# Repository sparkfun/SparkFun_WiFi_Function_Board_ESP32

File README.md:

SparkFun WiFi Function Board - ESP32
========================================

[*SparkFun WiFi Function Board - ESP32 (WRL-18430)*](https://www.sparkfun.com/products/18430)

The SparkFun MicroMod ESP32 Function Board adds additional wireless options to MicroMod Processor Boards that do not have that capability. This special function board acts as a coprocessor that takes advantage of Espressif's ESP32 WROOM to add WiFi and Bluetooth&reg; to your applications. 

At the core of the ESP32 WROOM module is the ESP32-D0WD-V3 chip which is designed to be both scalable and adaptive. ESP32 WROOM module on this board  features 16MB of flash memory, 520kB of internal SRAM, an integrated 802.11 b/g/n WiFi transceiver, and dual-mode Bluetooth capabilities. Utilizing our handy M.2 MicroMod connector, no soldering is required to connect it to your system. Simply match up the key on your processor and function board's beveled edge connector to their respective key on the M.2 connector, then secure them to the main board with screws. The ESP32 WROOM module can then be controlled using AT commands via the serial UART port.

The ESP32 Function Board comes pre-flashed with AT-command firmware and acts as a serial-to-WiFi gateway. Next to the module is a USB-C connector and CP2102 USB-to-serial converter. Whether you want to add AT commands of your own, or flash custom firmware on the ESP32, you can use this port to reprogram the ESP32.

Repository Contents
-------------------

* **/Hardware** - Eagle design files (.brd, .sch)
* **/Production** - Production panel files (.brd)

Documentation
--------------

* **[Hookup Guide](https://learn.sparkfun.com/tutorials/1998)** - Basic hookup guide

Product Versions
----------------

* [WRL-18430](https://www.sparkfun.com/products/18430) - Initial release

Version History
---------------

* v1.0 - Initial Release

License Information
-------------------

This product is _**open source**_! 

Please review the LICENSE.md file for license information. 

If you have any questions or concerns on licensing, please contact technical support on our [SparkFun forums](https://forum.sparkfun.com/viewforum.php?f=152).

Distributed as-is; no warranty is given.

- Your friends at SparkFun.

_<COLLABORATION CREDIT>_

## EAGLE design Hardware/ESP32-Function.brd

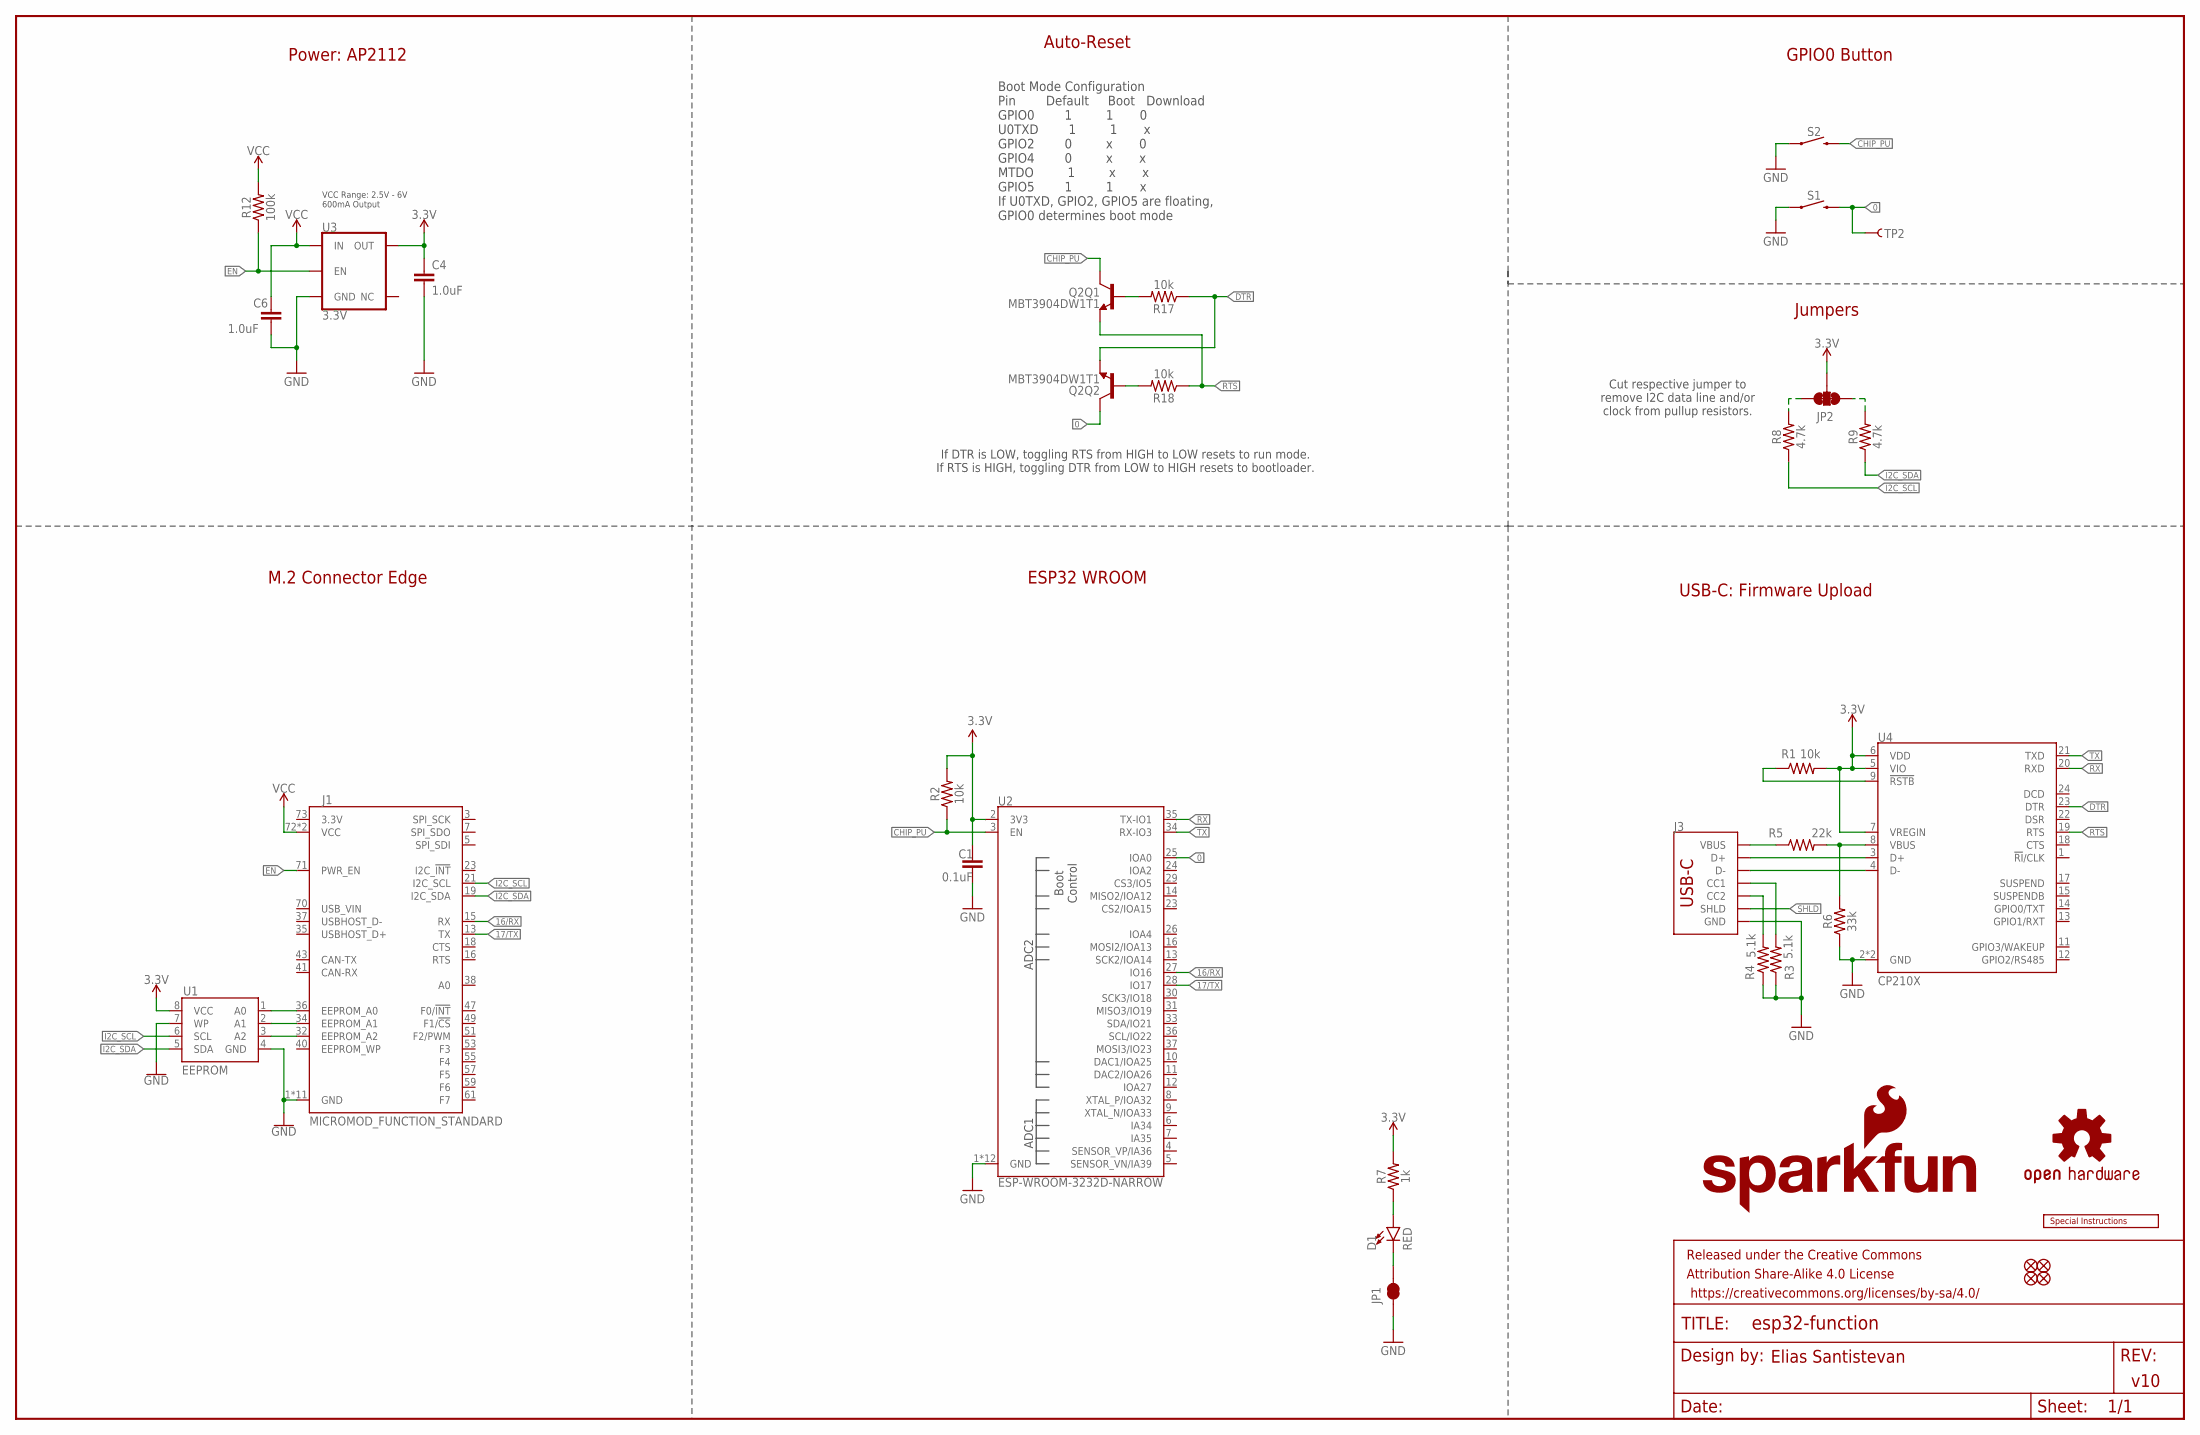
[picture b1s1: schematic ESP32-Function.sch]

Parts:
C1: 0.1uF; 0603
C4, C6: 1.0uF; 0603
D1: RED; LED-0603
FD1, FD2, FD3, FD4: FIDUCIAL1X2; FIDUCIAL-1X2
FRAME2: FRAME-LEDGER; CREATIVE_COMMONS
J1: MICROMOD_FUNCTION_STANDARD; M.2-CARD-E-22_FUNCTION_STANDARD
J3: USB_C_2-LAYER_PADS; USB-C-16P-2LAYER-PADS
JP1: JUMPER-SMT_2_NC_TRACE_SILK; SMT-JUMPER_2_NC_TRACE_SILK
JP2: JUMPER-SMT_3_2-NC_TRACE_SILK; SMT-JUMPER_3_2-NC_TRACE_SILK
LOGO1: SPECIAL_INSTRUCTIONS-ORDERING; ORDERING_INSTRUCTIONS
LOGO2: SFE_LOGO_NAME_FLAME.2_INCH; SFE_LOGO_NAME_FLAME_.2
LOGO3: OSHW-LOGOS; OSHW-LOGO-S
Q2: MBT3904DW1T1; SC70-6
R1, R2, R17, R18: 10k; 0603
R3, R4: 5.1k; 0603
R5: 22k; 0603
R6: 33k; 0603
R7: 1k; 0603
R8, R9: 4.7k; 0603
R12: 100k; 0603
S1, S2: MOMENTARY-SWITCH-SPST-SMD-5.2MM-TALL; TACTILE_SWITCH_SMD_5.2MM
TP2: TEST-POINTTP_15TH_THRU; TP_15TH
U1: EEPROM; SO08
U2: ESP-WROOM-3232D-NARROW; ESP-WROOM-32D-NARROW
U3: 3.3V; SOT23-5
U4: CP210X; QFN24

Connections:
0: Q2.6 (C), S1.3 (2), TP2.1, U2.25 (IOA0)
3.3V: C1.1, C4.1, JP2.2, R1.2, R2.2, R7.2, U1.8 (VCC), U2.2 (3V3), U3.5 (OUT), U4.5 (VIO), U4.6 (VDD), U4.7 (VREGIN)
16/RX: J1.15 (RX), U2.27 (IO16)
17/TX: J1.13 (TX), U2.28 (IO17)
CHIP_PU: Q2.3 (C), R2.1, S2.3 (2), U2.3 (EN)
D+: J3.A6 (D+), J3.B6 (D+), U4.3 (D+)
D-: J3.A7 (D-), J3.B7 (D-), U4.4 (D-)
DTR: Q2.1 (E), R17.1, U4.23 (DTR)
EN: J1.71 (PWR_EN), R12.1, U3.3 (EN)
GND: C1.2, C4.2, C6.2, J1.1 (GND), J1.33 (GND), J1.39 (GND), J1.45 (GND), J1.75 (GND), J1.GND1 (GND), J1.GND2 (GND), J1.GND3 (GND), J1.GND4 (GND), J1.GND5 (GND), J1.GND6 (GND), J3.GND, J3.GND2 (GND), JP1.1, R3.1, R4.1, R6.1, S1.1, S2.1, U1.4 (GND), U1.7 (WP), U2.1 (GND), U2.15 (GND), U2.38 (GND), U2.GND1 (GND), U2.GNDT1 (GND), U2.GNDT2 (GND), U2.GNDT3 (GND), U2.GNDT4 (GND), U2.GNDT5 (GND), U2.GNDT6 (GND), U2.GNDT7 (GND), U2.GNDT8 (GND), U3.2 (GND), U4.2 (GND), U4.PAD (GND)
I2C_SCL: J1.21 (I2C_SCL), R8.1, U1.6 (SCL)
I2C_SDA: J1.19 (I2C_SDA), R9.1, U1.5 (SDA)
unnamed: R1.1, U4.9 (!RSTB)
unnamed: J3.A5 (CC1), R3.2
unnamed: J3.VBUS1 (VBUS), J3.VBUS2 (VBUS), R5.1
unnamed: R5.2, R6.2, U4.8 (VBUS)
unnamed: J3.B5 (CC2), R4.2
unnamed: D1.C, JP1.2
unnamed: D1.A, R7.1
unnamed: J1.32 (EEPROM_A2), U1.3 (A2)
unnamed: J1.34 (EEPROM_A1), U1.2 (A1)
unnamed: Q2.5 (B), R17.2
unnamed: J1.36 (EEPROM_A0), U1.1 (A0)
unnamed: Q2.2 (B), R18.2
unnamed: JP2.1, R9.2
unnamed: JP2.3, R8.2
RTS: Q2.4 (E), R18.1, U4.19 (RTS)
RX: U2.35 (TX-IO1), U4.20 (RXD)
SHLD: J3.SHLD1 (SHLD), J3.SHLD2 (SHLD), J3.SHLD3 (SHLD), J3.SHLD4 (SHLD)
TX: U2.34 (RX-IO3), U4.21 (TXD)
VCC: C6.1, J1.72 (VCC), J1.74 (VCC), R12.2, U3.1 (IN)

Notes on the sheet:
Elias Santistevan
v10
Boot Mode Configuration Pin Default Boot Download GPIO0 1 1 0 U0TXD 1 1 x GPIO2 0 x 0 GPIO4 0 x x MTDO 1 x x GPIO5 1 1 x If U0TXD, GPIO2, GPIO5 are floating, GPIO0 determines boot mode
Auto-Reset
If DTR is LOW, toggling RTS from HIGH to LOW resets to run mode. If RTS is HIGH, toggling DTR from LOW to HIGH resets to bootloader.
VCC Range: 2.5V - 6V 600mA Output
Power: AP2112
ESP32 WROOM
M.2 Connector Edge
GPIO0 Button
USB-C: Firmware Upload
Jumpers
Cut respective jumper to remove I2C data line and/or clock from pullup resistors.

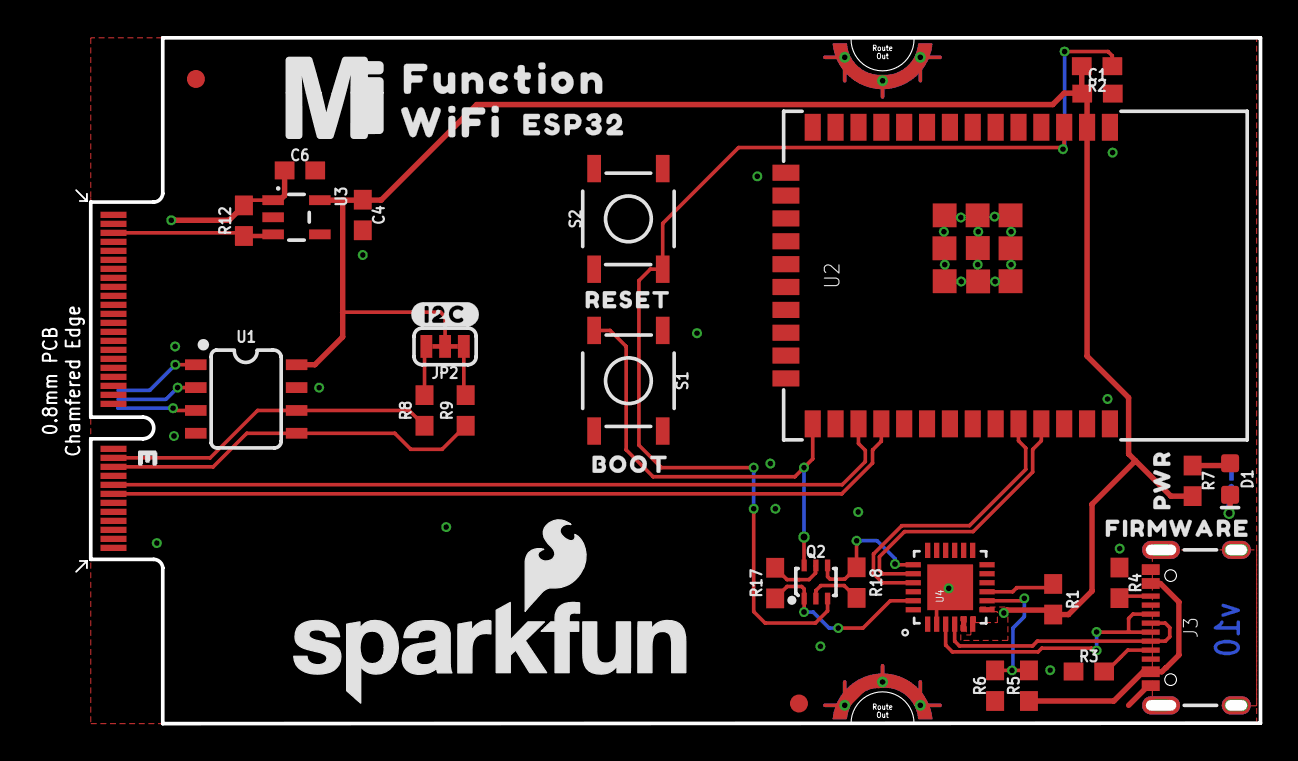
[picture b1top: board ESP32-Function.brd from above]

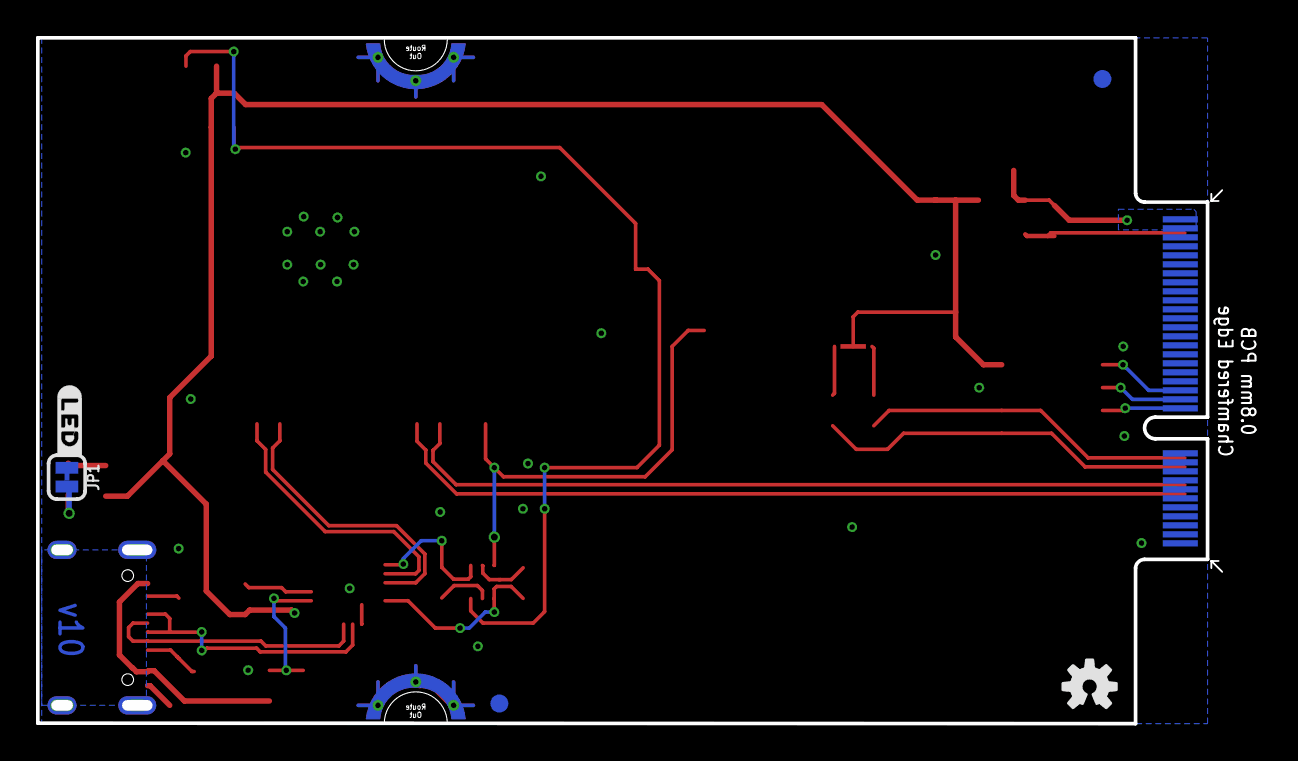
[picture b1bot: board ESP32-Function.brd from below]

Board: 2 copper layers, 67.5 x 37.7 mm, 46 parts (5 on the bottom side), 31 nets.

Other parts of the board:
U$1: BOOT3221
U$2: FUNCTION521
U$3: #I2C#1321540313558
U$4: ESP3212
U$5: RESET3220
U$6: MICROMOD_MI_LOGO_1
U$7: FIRMWARE3223
U$8: #LED#8
U$9: PWR3215
U$10: WIFI525

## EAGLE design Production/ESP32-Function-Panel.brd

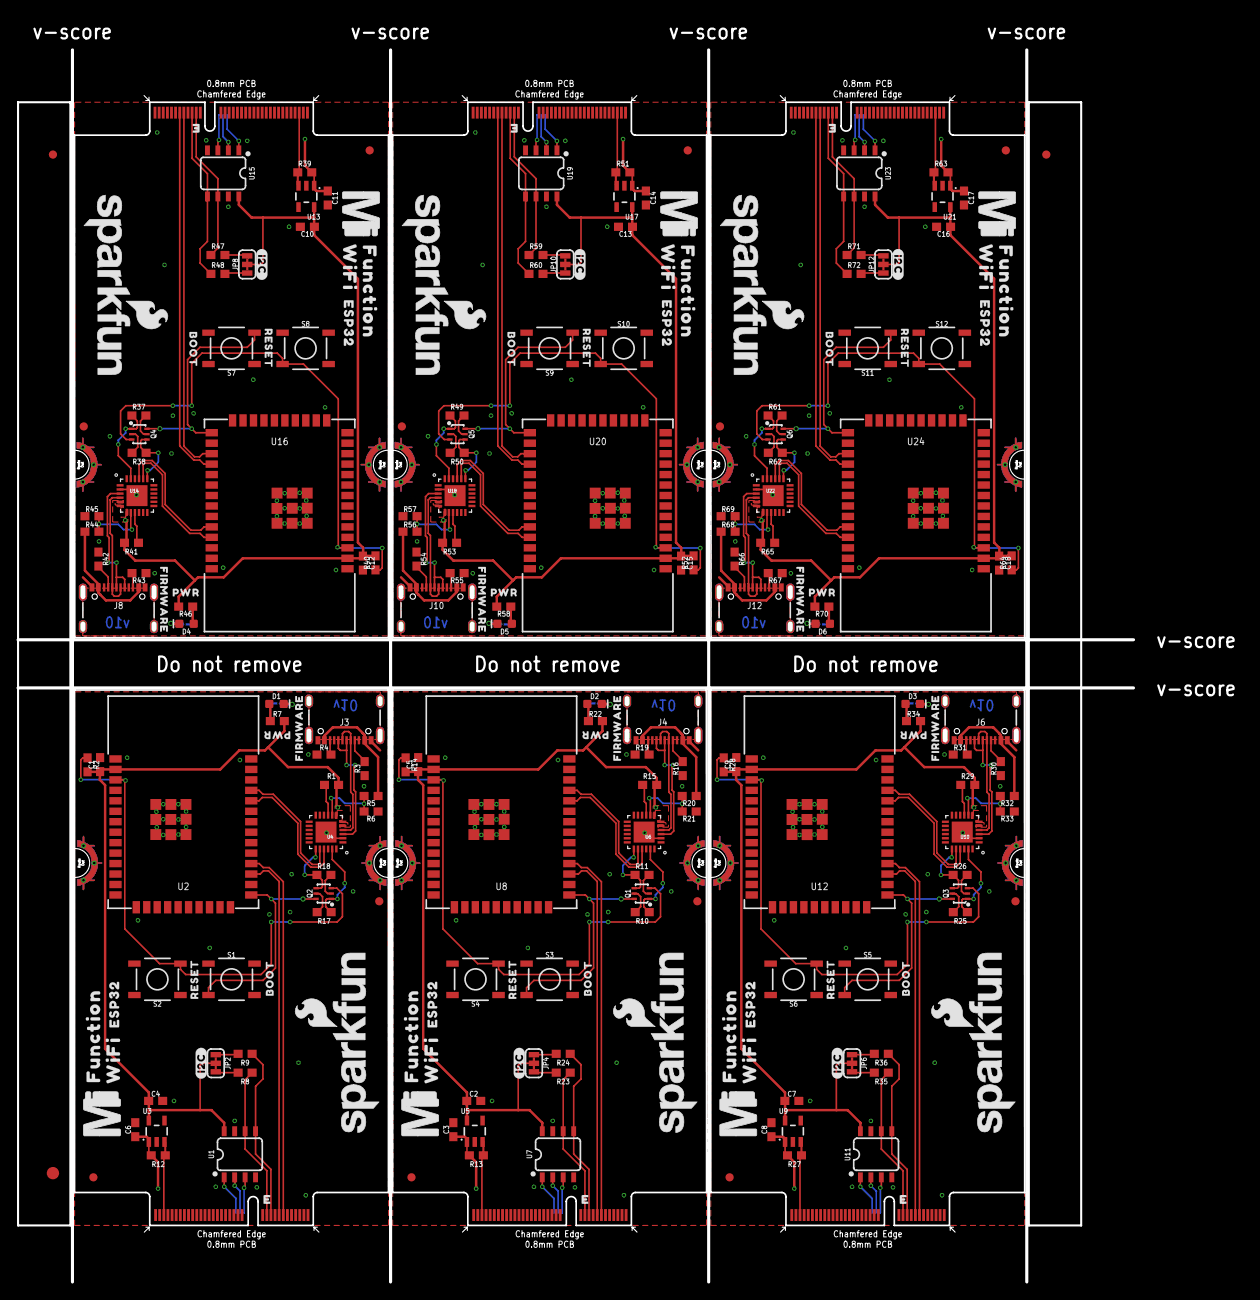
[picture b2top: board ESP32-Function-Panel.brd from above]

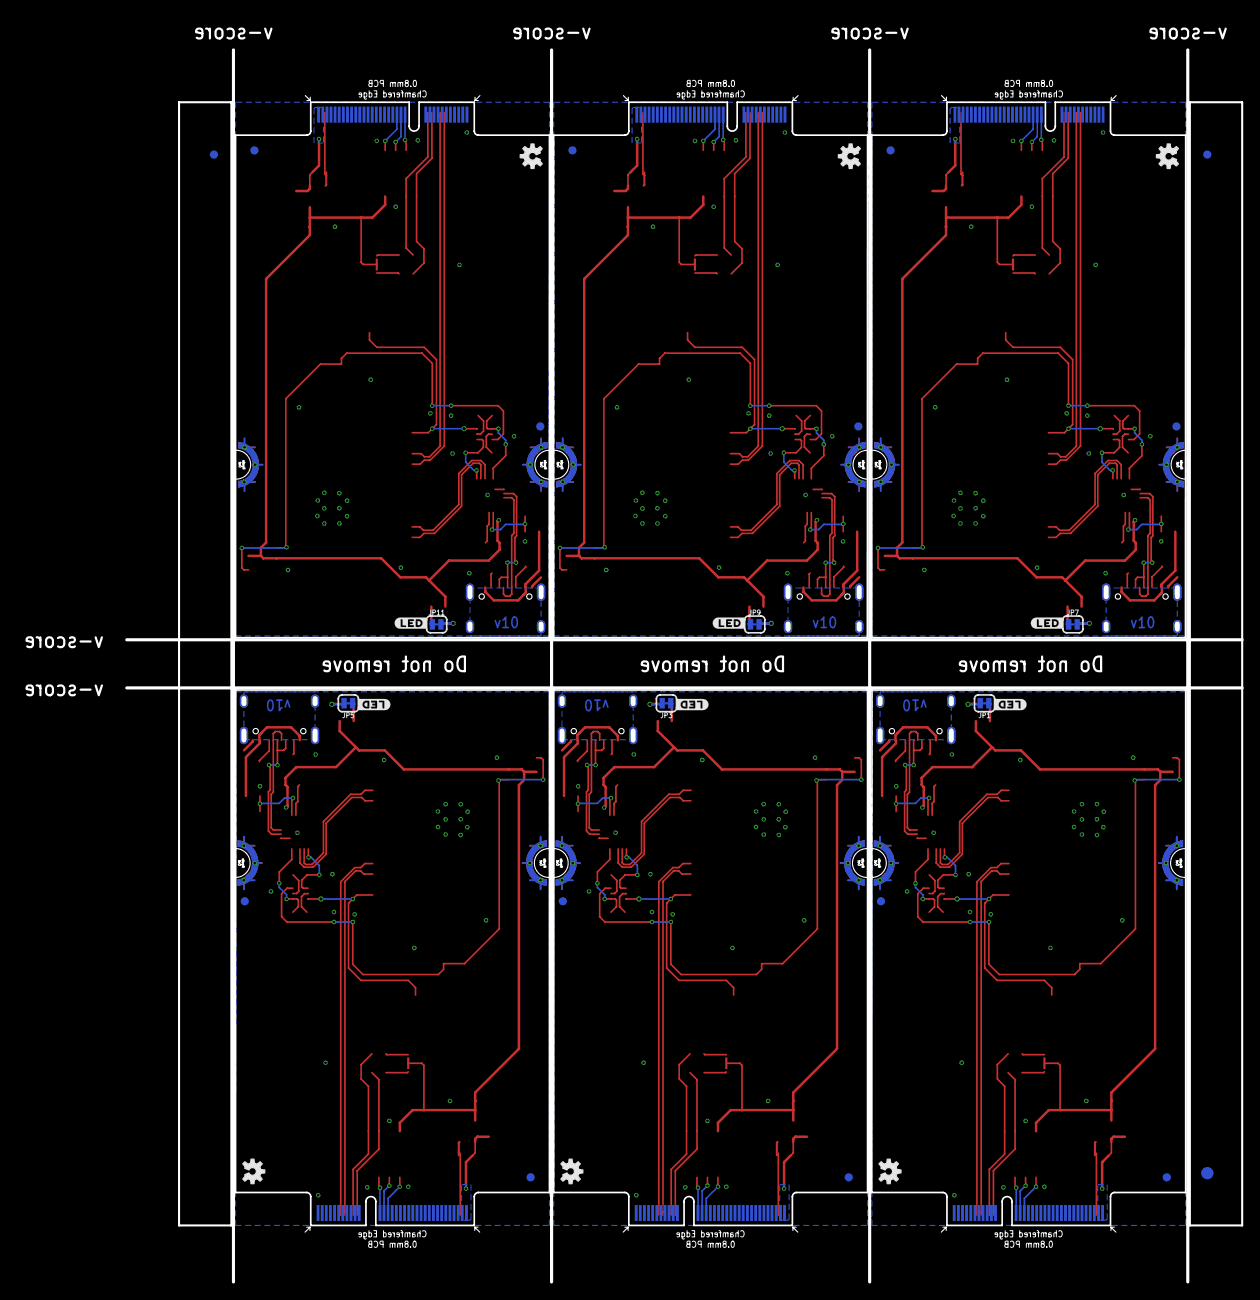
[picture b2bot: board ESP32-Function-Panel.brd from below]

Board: 2 copper layers, 148.4 x 153.2 mm, 270 parts (33 on the bottom side), 186 nets.

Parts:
C1, C5, C9, C12, C15, C18: 0.1uF; 0603
C2, C3, C4, C6, C7, C8, C10, C11, C13, C14, C16, C17: 1.0uF; 0603
D1, D2, D3, D4, D5, D6: RED; LED-0603
E$1, E$2, E$3, E$4: FIDUCIAL-1X2
E$5, E$6: FIDUCIAL-1.5X3
FD1, FD2, FD3, FD4, FD5, FD6, FD7, FD8, FD9, FD10, FD11, FD12, FD13, FD14, FD15, FD16, FD17, FD18, FD19, FD20, FD21, FD22, FD23, FD24: FIDUCIAL1X2; FIDUCIAL-1X2
J1, J2, J5, J7, J9, J11: MICROMOD_STANDARD; M.2-CARD-E-22_FUNCTION_STANDARD
J3, J4, J6, J8, J10, J12: USB-C-16P-2LAYER-PADS
JP1, JP3, JP5, JP7, JP9, JP11: JUMPER-SMT_2_NC_TRACE_SILK; SMT-JUMPER_2_NC_TRACE_SILK
JP2, JP4, JP6, JP8, JP10, JP12: JUMPER-SMT_3_2-NC_TRACE_SILK; SMT-JUMPER_3_2-NC_TRACE_SILK
LOGO1, LOGO2, LOGO5, LOGO7, LOGO9, LOGO11: SFE_LOGO_NAME_FLAME.2_INCH; SFE_LOGO_NAME_FLAME_.2
LOGO3, LOGO4, LOGO6, LOGO8, LOGO10, LOGO12: OSHW-LOGOS; OSHW-LOGO-S
Q1, Q2, Q3, Q4, Q5, Q6: MBT3904DW1T1; SC70-6
R1, R2, R10, R11, R14, R15, R17, R18, R25, R26, R28, R29, R37, R38, R40, R41, R49, R50, R52, R53, R61, R62, R64, R65: 10k; 0603
R3, R4, R16, R19, R30, R31, R42, R43, R54, R55, R66, R67: 5.1k; 0603
R5, R20, R32, R44, R56, R68: 22k; 0603
R6, R21, R33, R45, R57, R69: 33k; 0603
R7, R22, R34, R46, R58, R70: 1k; 0603
R8, R9, R23, R24, R35, R36, R47, R48, R59, R60, R71, R72: 4.7k; 0603
R12, R13, R27, R39, R51, R63: 100k; 0603
S1, S2, S3, S4, S5, S6, S7, S8, S9, S10, S11, S12: MOMENTARY-SWITCH-SPST-SMD-5.2MM-TALL; TACTILE_SWITCH_SMD_5.2MM
TP1, TP2, TP3, TP4, TP5, TP6: TEST-POINTTP_15TH_THRU; TP_15TH
U1, U7, U11, U15, U19, U23: EEPROM; SO08
U2, U8, U12, U16, U20, U24: ESP-WROOM-3232D-NARROW; ESP-WROOM-32D-NARROW
U3, U5, U9, U13, U17, U21: 3.3V; SOT23-5
U4, U6, U10, U14, U18, U22: CP210X; QFN24
U$1, U$11, U$21, U$31, U$41, U$51: BOOT3221
U$2, U$17, U$27, U$37, U$47, U$57: FUNCTION521
U$3, U$20, U$30, U$40, U$50, U$60: #I2C#1321540313558
U$4, U$12, U$22, U$32, U$42, U$52: ESP3212
U$5, U$14, U$24, U$34, U$44, U$54: RESET3220
U$6, U$18, U$28, U$38, U$48, U$58: MICROMOD_MI_LOGO_1
U$7, U$13, U$23, U$33, U$43, U$53: FIRMWARE3223
U$8, U$15, U$25, U$35, U$45, U$55: #LED#8
U$9, U$16, U$26, U$36, U$46, U$56: PWR3215
U$10, U$19, U$29, U$39, U$49, U$59: WIFI525

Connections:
0: Q2.6, S1.3, TP2.1, U2.25
1: Q1.6, S3.3, TP1.1, U8.25
2: Q3.6, S5.3, TP3.1, U12.25
3: Q4.6, S7.3, TP4.1, U16.25
3.3V: C1.1, C4.1, JP2.2, R1.2, R2.2, R7.2, U1.8, U2.2, U3.5, U4.5, U4.6, U4.7
3.3V1: C2.1, C5.1, JP4.2, R14.2, R15.2, R22.2, U5.5, U6.5, U6.6, U6.7, U7.8, U8.2
3.3V2: C7.1, C9.1, JP6.2, R28.2, R29.2, R34.2, U9.5, U10.5, U10.6, U10.7, U11.8, U12.2
3.3V3: C10.1, C12.1, JP8.2, R40.2, R41.2, R46.2, U13.5, U14.5, U14.6, U14.7, U15.8, U16.2
3.3V4: C13.1, C15.1, JP10.2, R52.2, R53.2, R58.2, U17.5, U18.5, U18.6, U18.7, U19.8, U20.2
3.3V5: C16.1, C18.1, JP12.2, R64.2, R65.2, R70.2, U21.5, U22.5, U22.6, U22.7, U23.8, U24.2
4: Q5.6, S9.3, TP5.1, U20.25
5: Q6.6, S11.3, TP6.1, U24.25
16/RX: J1.15, U2.27
16/RX1: J2.15, U8.27
16/RX2: J5.15, U12.27
16/RX3: J7.15, U16.27
16/RX4: J9.15, U20.27
16/RX5: J11.15, U24.27
17/TX: J1.13, U2.28
17/TX1: J2.13, U8.28
17/TX2: J5.13, U12.28
17/TX3: J7.13, U16.28
17/TX4: J9.13, U20.28
17/TX5: J11.13, U24.28
CHIP_PU: Q2.3, R2.1, S2.3, U2.3
CHIP_PU1: Q1.3, R14.1, S4.3, U8.3
CHIP_PU2: Q3.3, R28.1, S6.3, U12.3
CHIP_PU3: Q4.3, R40.1, S8.3, U16.3
CHIP_PU4: Q5.3, R52.1, S10.3, U20.3
CHIP_PU5: Q6.3, R64.1, S12.3, U24.3
D+: J3.A6, J3.B6, U4.3
D+1: J4.A6, J4.B6, U6.3
D+2: J6.A6, J6.B6, U10.3
D+3: J8.A6, J8.B6, U14.3
D+4: J10.A6, J10.B6, U18.3
D+5: J12.A6, J12.B6, U22.3
D-: J3.A7, J3.B7, U4.4
D-1: J4.A7, J4.B7, U6.4
D-2: J6.A7, J6.B7, U10.4
D-3: J8.A7, J8.B7, U14.4
D-4: J10.A7, J10.B7, U18.4
D-5: J12.A7, J12.B7, U22.4
DTR: Q2.1, R17.1, U4.23
DTR1: Q1.1, R10.1, U6.23
DTR2: Q3.1, R25.1, U10.23
DTR3: Q4.1, R37.1, U14.23
DTR4: Q5.1, R49.1, U18.23
DTR5: Q6.1, R61.1, U22.23
EN: J1.71, R12.1, U3.3
EN1: J2.71, R13.1, U5.3
EN2: J5.71, R27.1, U9.3
EN3: J7.71, R39.1, U13.3
EN4: J9.71, R51.1, U17.3
EN5: J11.71, R63.1, U21.3
GND: C1.2, C4.2, C6.2, J1.1, J1.33, J1.39, J1.45, J1.75, J1.GND1, J1.GND2, J1.GND3, J1.GND4, J1.GND5, J1.GND6, J3.GND, J3.GND2, JP1.1, R3.1, R4.1, R6.1, S1.1, S2.1, U1.4, U1.7, U2.1, U2.15, U2.38, U2.GND1, U2.GNDT1, U2.GNDT2, U2.GNDT3, U2.GNDT4, U2.GNDT5, U2.GNDT6, U2.GNDT7, U2.GNDT8, U3.2, U4.2, U4.PAD
GND1: C2.2, C3.2, C5.2, J2.1, J2.33, J2.39, J2.45, J2.75, J2.GND1, J2.GND2, J2.GND3, J2.GND4, J2.GND5, J2.GND6, J4.GND, J4.GND2, JP3.1, R16.1, R19.1, R21.1, S3.1, S4.1, U5.2, U6.2, U6.PAD, U7.4, U7.7, U8.1, U8.15, U8.38, U8.GND1, U8.GNDT1, U8.GNDT2, U8.GNDT3, U8.GNDT4, U8.GNDT5, U8.GNDT6, U8.GNDT7, U8.GNDT8
GND2: C7.2, C8.2, C9.2, J5.1, J5.33, J5.39, J5.45, J5.75, J5.GND1, J5.GND2, J5.GND3, J5.GND4, J5.GND5, J5.GND6, J6.GND, J6.GND2, JP5.1, R30.1, R31.1, R33.1, S5.1, S6.1, U9.2, U10.2, U10.PAD, U11.4, U11.7, U12.1, U12.15, U12.38, U12.GND1, U12.GNDT1, U12.GNDT2, U12.GNDT3, U12.GNDT4, U12.GNDT5, U12.GNDT6, U12.GNDT7, U12.GNDT8
GND3: C10.2, C11.2, C12.2, J7.1, J7.33, J7.39, J7.45, J7.75, J7.GND1, J7.GND2, J7.GND3, J7.GND4, J7.GND5, J7.GND6, J8.GND, J8.GND2, JP7.1, R42.1, R43.1, R45.1, S7.1, S8.1, U13.2, U14.2, U14.PAD, U15.4, U15.7, U16.1, U16.15, U16.38, U16.GND1, U16.GNDT1, U16.GNDT2, U16.GNDT3, U16.GNDT4, U16.GNDT5, U16.GNDT6, U16.GNDT7, U16.GNDT8
GND4: C13.2, C14.2, C15.2, J9.1, J9.33, J9.39, J9.45, J9.75, J9.GND1, J9.GND2, J9.GND3, J9.GND4, J9.GND5, J9.GND6, J10.GND, J10.GND2, JP9.1, R54.1, R55.1, R57.1, S9.1, S10.1, U17.2, U18.2, U18.PAD, U19.4, U19.7, U20.1, U20.15, U20.38, U20.GND1, U20.GNDT1, U20.GNDT2, U20.GNDT3, U20.GNDT4, U20.GNDT5, U20.GNDT6, U20.GNDT7, U20.GNDT8
GND5: C16.2, C17.2, C18.2, J11.1, J11.33, J11.39, J11.45, J11.75, J11.GND1, J11.GND2, J11.GND3, J11.GND4, J11.GND5, J11.GND6, J12.GND, J12.GND2, JP11.1, R66.1, R67.1, R69.1, S11.1, S12.1, U21.2, U22.2, U22.PAD, U23.4, U23.7, U24.1, U24.15, U24.38, U24.GND1, U24.GNDT1, U24.GNDT2, U24.GNDT3, U24.GNDT4, U24.GNDT5, U24.GNDT6, U24.GNDT7, U24.GNDT8
I2C_SCL: J1.21, R8.1, U1.6
I2C_SCL1: J2.21, R23.1, U7.6
I2C_SCL2: J5.21, R35.1, U11.6
I2C_SCL3: J7.21, R47.1, U15.6
I2C_SCL4: J9.21, R59.1, U19.6
I2C_SCL5: J11.21, R71.1, U23.6
I2C_SDA: J1.19, R9.1, U1.5
I2C_SDA1: J2.19, R24.1, U7.5
I2C_SDA2: J5.19, R36.1, U11.5
I2C_SDA3: J7.19, R48.1, U15.5
I2C_SDA4: J9.19, R60.1, U19.5
I2C_SDA5: J11.19, R72.1, U23.5
unnamed: R1.1, U4.9
unnamed: J3.A5, R3.2
unnamed: J3.VBUS1, J3.VBUS2, R5.1
unnamed: R5.2, R6.2, U4.8
unnamed: J3.B5, R4.2
unnamed: D1.C, JP1.2
unnamed: D1.A, R7.1
unnamed: J1.32, U1.3
unnamed: J1.34, U1.2
unnamed: Q2.5, R17.2
unnamed: J1.36, U1.1
unnamed: Q2.2, R18.2
unnamed: JP2.1, R9.2
unnamed: JP2.3, R8.2
unnamed: Q1.5, R10.2
unnamed: Q1.2, R11.2
unnamed: J4.A5, R16.2
unnamed: J4.B5, R19.2
unnamed: R15.1, U6.9
unnamed: J4.VBUS1, J4.VBUS2, R20.1
unnamed: R20.2, R21.2, U6.8
unnamed: D2.C, JP3.2
unnamed: D2.A, R22.1
unnamed: J2.32, U7.3
unnamed: J2.34, U7.2
unnamed: J2.36, U7.1
unnamed: JP4.1, R24.2
unnamed: JP4.3, R23.2
unnamed: Q3.5, R25.2
unnamed: Q3.2, R26.2
unnamed: J6.A5, R30.2
unnamed: J6.B5, R31.2
unnamed: R29.1, U10.9
unnamed: J6.VBUS1, J6.VBUS2, R32.1
unnamed: R32.2, R33.2, U10.8
unnamed: D3.C, JP5.2
unnamed: D3.A, R34.1
unnamed: J5.32, U11.3
unnamed: J5.34, U11.2
unnamed: J5.36, U11.1
unnamed: JP6.1, R36.2
unnamed: JP6.3, R35.2
unnamed: Q4.5, R37.2
unnamed: Q4.2, R38.2
unnamed: J8.A5, R42.2
unnamed: J8.B5, R43.2
unnamed: R41.1, U14.9
unnamed: J8.VBUS1, J8.VBUS2, R44.1
unnamed: R44.2, R45.2, U14.8
unnamed: D4.C, JP7.2
unnamed: D4.A, R46.1
unnamed: J7.32, U15.3
unnamed: J7.34, U15.2
unnamed: J7.36, U15.1
unnamed: JP8.1, R48.2
unnamed: JP8.3, R47.2
unnamed: Q5.5, R49.2
unnamed: Q5.2, R50.2
unnamed: J10.A5, R54.2
unnamed: J10.B5, R55.2
unnamed: R53.1, U18.9
unnamed: J10.VBUS1, J10.VBUS2, R56.1
unnamed: R56.2, R57.2, U18.8
unnamed: D5.C, JP9.2
unnamed: D5.A, R58.1
unnamed: J9.32, U19.3
unnamed: J9.34, U19.2
unnamed: J9.36, U19.1
unnamed: JP10.1, R60.2
unnamed: JP10.3, R59.2
unnamed: Q6.5, R61.2
unnamed: Q6.2, R62.2
unnamed: J12.A5, R66.2
unnamed: J12.B5, R67.2
unnamed: R65.1, U22.9
unnamed: J12.VBUS1, J12.VBUS2, R68.1
unnamed: R68.2, R69.2, U22.8
unnamed: D6.C, JP11.2
unnamed: D6.A, R70.1
unnamed: J11.32, U23.3
unnamed: J11.34, U23.2
unnamed: J11.36, U23.1
unnamed: JP12.1, R72.2
unnamed: JP12.3, R71.2
RTS: Q2.4, R18.1, U4.19
RTS1: Q1.4, R11.1, U6.19
RTS2: Q3.4, R26.1, U10.19
RTS3: Q4.4, R38.1, U14.19
RTS4: Q5.4, R50.1, U18.19
RTS5: Q6.4, R62.1, U22.19
RX: U2.35, U4.20
RX1: U6.20, U8.35
RX2: U10.20, U12.35
RX3: U14.20, U16.35
RX4: U18.20, U20.35
RX5: U22.20, U24.35
SHLD: J3.SHLD1, J3.SHLD2, J3.SHLD3, J3.SHLD4
SHLD1: J4.SHLD1, J4.SHLD2, J4.SHLD3, J4.SHLD4
SHLD2: J6.SHLD1, J6.SHLD2, J6.SHLD3, J6.SHLD4
SHLD3: J8.SHLD1, J8.SHLD2, J8.SHLD3, J8.SHLD4
SHLD4: J10.SHLD1, J10.SHLD2, J10.SHLD3, J10.SHLD4
SHLD5: J12.SHLD1, J12.SHLD2, J12.SHLD3, J12.SHLD4
TX: U2.34, U4.21
TX1: U6.21, U8.34
TX2: U10.21, U12.34
TX3: U14.21, U16.34
TX4: U18.21, U20.34
TX5: U22.21, U24.34
VCC: C6.1, J1.72, J1.74, R12.2, U3.1
VCC1: C3.1, J2.72, J2.74, R13.2, U5.1
VCC2: C8.1, J5.72, J5.74, R27.2, U9.1
VCC3: C11.1, J7.72, J7.74, R39.2, U13.1
VCC4: C14.1, J9.72, J9.74, R51.2, U17.1
VCC5: C17.1, J11.72, J11.74, R63.2, U21.1

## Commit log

2021-08-17 Initial commit (post-prototype, pre-finalized-for-REDs)
2021-09-01 Moves to 0603 components where able, adds silk, fixes traces affected by move to 0603
    * removes wire stubs
    * Fixes random air wires
2021-09-10 Adds I2C pullups and jumper to remove them, rearranges silk
2021-09-10 Panel v10
2021-09-13 Moves production files to correct location
2021-09-27 Adds pullup resistor and jumper to write protect net, brings write protect trace to card's edge
2021-11-03 Updates function board symbol
2021-11-11 Updates the design to use the Micromod-function device in the official SFE Eagle Libs

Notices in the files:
parts and their libraries:
SparkFun-Aesthetics: Licensing: Creative Commons ShareAlike 4.0 International - https://creativecommons.org/licenses/by-sa/4.0
SparkFun-Aesthetics: Released under the Creative Commons Attribution Share-Alike 4.0 License
SparkFun-Aesthetics: https://creativecommons.org/licenses/by-sa/4.0
